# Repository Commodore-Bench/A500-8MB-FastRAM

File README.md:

# A500-8MB-FastRAM

8MB FastRAM Board for the Amiga 500 &amp; Amiga 500+

This board is based on the A600 8MB FastRAM board here: http://lvd.nedopc.com/Projects/a600_8mb/index.html

As such, the schematic is a derivative/fork of the original design, to accommodate it's usage in A500's (might also work in A1000's & A2000's).

Everything has been designed to be as easy to solder as possible, minimal surface mount, with the exception of the memory modules, but they're SOJ-42, which should be easy enough even with a basic soldering iron.

The code for the CPLD has been mostly unchanged from the original, just a single letter changed to reflect usage in the A500 as opposed to the A600, along with renaming the signal pins to something simpler.

There is only 16 MB of addressable space on 68000 CPU. This board uses half of that space, residing at $200000-$9FFFFF Zorro II memory address range. It does autoconfigure, so no need to do anything in the DOS shell.

The original design used an Altera EPM7032 5v CPLD - this has been changed for an Atmel ATF1502ASV - as these are pin-compatible replacements. 

# Bill of Materials

1 x TI TPS7333QP - https://www.mouser.co.uk/ProductDetail/Texas-Instruments/TPS7333QP?qs=sGAEpiMZZMsGz1a6aV8DcPXeWoVS0FnzG9Q6QtE79H4%3D

2 x 74AHCT157N - https://www.mouser.co.uk/ProductDetail/Texas-Instruments/SN74AHCT157N?qs=sGAEpiMZZMtxONTBFIcRfgMIbQHDmxevRGwLkGEQEjo%3D

4 x ISSI IS41LV6100D-50KLI - https://www.mouser.co.uk/ProductDetail/ISSI/IS41LV16100D-50KLI?qs=sGAEpiMZZMti5BT4iPSEnceOTYqGrIvVPVYLC4ueHfI%3D

1 x Microchip ATF1502ASV-15JU44 - https://www.digikey.co.uk/product-detail/en/microchip-technology/ATF1502ASV-15JU44/ATF1502ASV-15JU44-ND/1008571

18 x 0.1uF X7R MLCC Capacitors - https://www.mouser.co.uk/ProductDetail/Vishay/A104M15X7RF5TAA?qs=sGAEpiMZZMt3KoXD5rJ2N0XmixHAufRxOaDBAbHwq68%3D

3 x 10k Metal Film Resistors - https://www.mouser.co.uk/ProductDetail/Yageo/MFR-25FRF52-10K?qs=sGAEpiMZZMu61qfTUdNhGztMfEiwFKKTpKeEBKehEYg%3D

1 x DIP-8 Socket - https://www.mouser.co.uk/ProductDetail/Mill-Max/115-47-308-41-001000?qs=sGAEpiMZZMs%2FSh%2Fkjph1tkCPjfxlAKUmvzlAYtWANYQ%3D

2 x DIP-16 Socket - https://www.mouser.co.uk/ProductDetail/Mill-Max/115-47-316-41-001000?qs=sGAEpiMZZMs%2FSh%2Fkjph1tkCPjfxlAKUmVX4IEPiLC6M%3D

1 x DIP-64 Socket - https://www.mouser.co.uk/ProductDetail/Mill-Max/110-93-964-41-001000?qs=sGAEpiMZZMs%2FSh%2Fkjph1tvt1%2FmEPT%2FXoOM6K6uUd7C4%3D

1 x PLCC-44 Socket - https://www.mouser.co.uk/ProductDetail/Mill-Max/940-44-044-24-000000?qs=sGAEpiMZZMs%2FSh%2Fkjph1tvt1%2FmEPT%2FXokeuUw4hSJ6E%3D

2 x SIL-32 Headers - https://www.mouser.co.uk/ProductDetail/Harwin/M20-9993246?qs=sGAEpiMZZMs%252BGHln7q6pmzlZUuX%2F53qjvbFdqJAMwHI%3D

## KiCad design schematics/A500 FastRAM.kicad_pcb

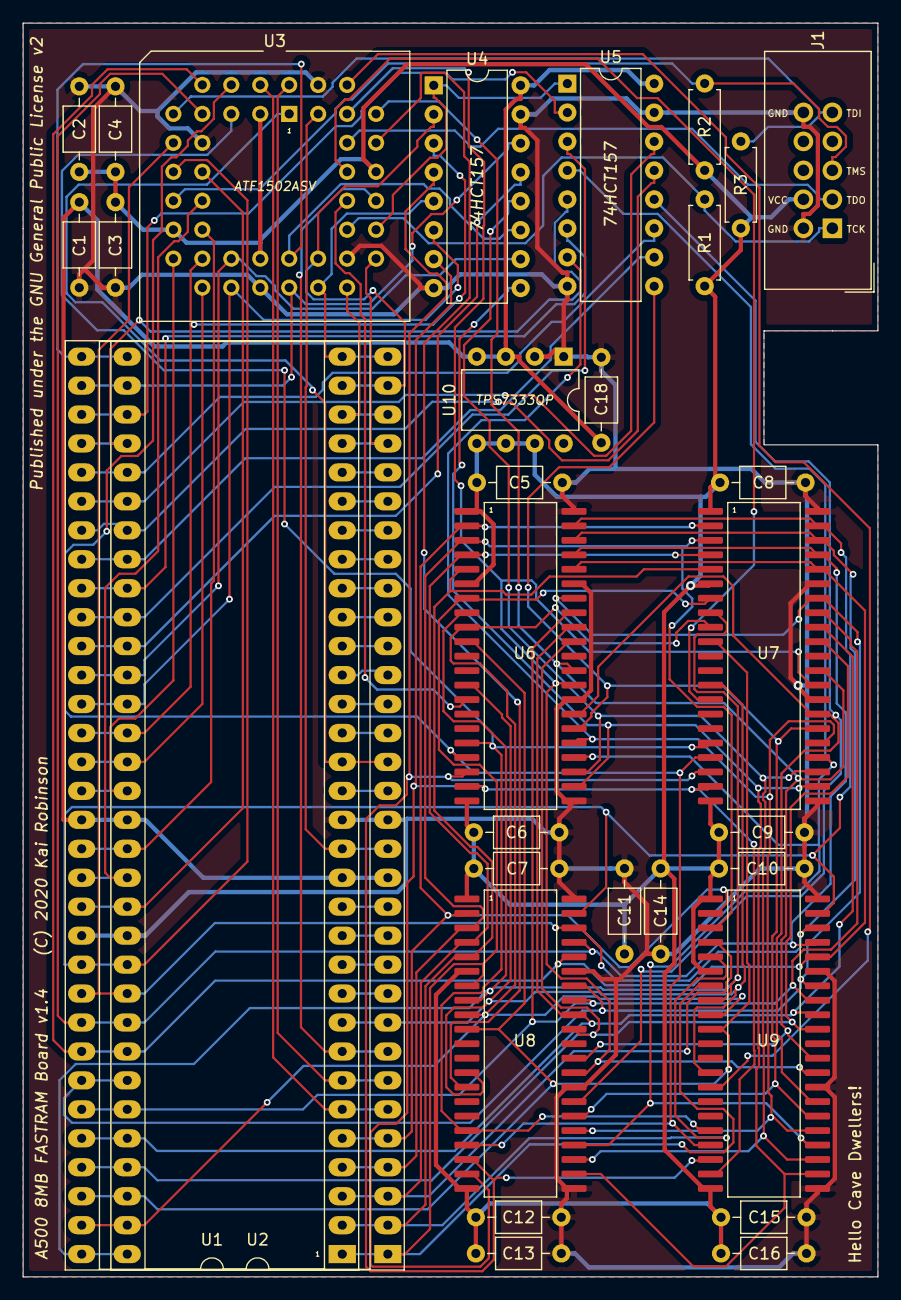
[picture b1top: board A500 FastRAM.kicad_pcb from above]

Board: 2 copper layers, 75.0 x 110.0 mm, 31 parts (0 on the bottom side), 84 nets.

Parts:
C1, C2, C3, C4, C5, C6, C7, C8, C9, C10, C11, C12, C13, C14, C15, C16, C18: 0.1uF; C_Axial_L3.8mm_D2.6mm_P7.50mm_Horizontal
J1: Microsemi_FlashPro-JTAG-10; IDC-Header_2x05_P2.54mm_Vertical
R1, R2, R3: 10k; R_Axial_DIN0207_L6.3mm_D2.5mm_P7.62mm_Horizontal
U1: 68000 Boardside; DIP-64_W22.86mm_Socket_LongPads
U2: 68000 Socket; DIP-64_W22.86mm_Socket_LongPads
U3: ATF1502ASV-15JU44; PLCC-44_THT-Socket
U4, U5: 74157; DIP-16_W7.62mm
U6, U7, U8, U9: IS41LV16100D; SOJ-42
U10: TPS7333QP; DIP-8_W7.62mm

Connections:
/CPU_A1: U1.29, U2.29, U3.29
/CPU_A2: U1.30, U2.30, U3.28
/CPU_A3: U1.31, U2.31, U3.27, U4.2
/CPU_A4: U1.32, U2.32, U3.26, U4.5
/CPU_A5: U1.33, U2.33, U3.25, U4.11
/CPU_A6: U1.34, U2.34, U3.24, U4.14
/CPU_A7: U1.35, U2.35, U5.2
/CPU_A8: U1.36, U2.36, U5.5
/CPU_A9: U1.37, U2.37, U5.11
/CPU_A10: U1.38, U2.38, U5.14
/CPU_A11: U1.39, U2.39, U5.13
/CPU_A12: U1.40, U2.40, U5.10
/CPU_A13: U1.41, U2.41, U5.6
/CPU_A14: U1.42, U2.42, U5.3
/CPU_A15: U1.43, U2.43, U4.13
/CPU_A16: U1.44, U2.44, U3.21, U4.10
/CPU_A17: U1.45, U2.45, U3.20, U4.6
/CPU_A18: U1.46, U2.46, U3.19, U4.3
/CPU_A19: U1.47, U2.47, U3.18
/CPU_A20: U1.48, U2.48, U3.17
/CPU_A21: U1.50, U2.50, U3.16
/CPU_A22: U1.51, U2.51, U3.14
/CPU_A23: U1.52, U2.52, U3.12
/CPU_AS: U1.6, U2.6, U3.2
/CPU_BERR: U1.22, U2.22
/CPU_BG: U1.11, U2.11
/CPU_BGACK: U1.12, U2.12
/CPU_BR: U1.13, U2.13
/CPU_CLK: U1.15, U2.15, U3.43
/CPU_D0: U1.5, U2.5, U6.2, U7.2, U8.2, U9.2
/CPU_D1: U1.4, U2.4, U6.3, U7.3, U8.3, U9.3
/CPU_D2: U1.3, U2.3, U6.4, U7.4, U8.4, U9.4
/CPU_D3: U1.2, U2.2, U6.5, U7.5, U8.5, U9.5
/CPU_D4: U1.1, U2.1, U6.7, U7.7, U8.7, U9.7
/CPU_D5: U1.64, U2.64, U6.8, U7.8, U8.8, U9.8
/CPU_D6: U1.63, U2.63, U6.9, U7.9, U8.9, U9.9
/CPU_D7: U1.62, U2.62, U6.10, U7.10, U8.10, U9.10
/CPU_D8: U1.61, U2.61, U6.33, U7.33, U8.33, U9.33
/CPU_D9: U1.60, U2.60, U6.34, U7.34, U8.34, U9.34
/CPU_D10: U1.59, U2.59, U6.35, U7.35, U8.35, U9.35
/CPU_D11: U1.58, U2.58, U6.36, U7.36, U8.36, U9.36
/CPU_D12: U1.57, U2.57, U3.6, U6.38, U7.38, U8.38, U9.38
/CPU_D13: U1.56, U2.56, U3.8, U6.39, U7.39, U8.39, U9.39
/CPU_D14: U1.55, U2.55, U3.9, U6.40, U7.40, U8.40, U9.40
/CPU_D15: U1.54, U2.54, U3.11, U6.41, U7.41, U8.41, U9.41
/CPU_DTACK: U1.10, U2.10
/CPU_E: U1.20, U2.20
/CPU_FC0: U1.28, U2.28
/CPU_FC1: U1.27, U2.27
/CPU_FC2: U1.26, U2.26
/CPU_HALT: U1.17, U2.17
/CPU_IPL0: U1.25, U2.25
/CPU_IPL1: U1.24, U2.24
/CPU_IPL2: U1.23, U2.23
/CPU_LDS: U1.8, U2.8, U3.33
/CPU_RESET: U1.18, U2.18, U3.1
/CPU_RW: U1.9, U2.9, U6.13, U7.13, U8.13, U9.13
/CPU_UDS: U1.7, U2.7, U3.44
/CPU_VMA: U1.19, U2.19
/CPU_VPA: U1.21, U2.21
/DRAM_A0: U3.5, U6.17, U7.17, U8.17, U9.17
/DRAM_A1: U3.4, U6.18, U7.18, U8.18, U9.18
/DRAM_A2: U4.4, U6.19, U7.19, U8.19, U9.19
/DRAM_A3: U4.7, U6.20, U7.20, U8.20, U9.20
/DRAM_A4: U4.9, U6.23, U7.23, U8.23, U9.23
/DRAM_A5: U4.12, U6.24, U7.24, U8.24, U9.24
/DRAM_A6: U5.4, U6.25, U7.25, U8.25, U9.25
/DRAM_A7: U5.7, U6.26, U7.26, U8.26, U9.26
/DRAM_A8: U5.9, U6.27, U7.27, U8.27, U9.27
/DRAM_A9: U5.12, U6.28, U7.28, U8.28, U9.28
/DRAM_LCAS: U3.39, U6.31, U7.31, U8.31, U9.31
/DRAM_RAS0: U3.34, U6.14
/DRAM_RAS1: U3.36, U7.14
/DRAM_RAS2: U3.37, U8.14
/DRAM_RAS3: U3.40, U9.14
/DRAM_UCAS: U3.41, U6.30, U7.30, U8.30, U9.30
/MUX_SWITCH: U3.31, U4.1, U5.1
/TCK: J1.1, R1.2, U3.32
/TDI: J1.9, R3.2, U3.7
/TDO: J1.3, U3.38
/TMS: J1.5, R2.2, U3.13
/VCC33: C2.2, C3.1, C4.2, C5.1, C6.1, C7.1, C8.1, C9.1, C10.1, C11.1, C12.1, C13.1, C14.1, C15.1, C16.1, J1.4, R1.1, R2.1, R3.1, U3.3, U3.15, U3.23, U3.35, U6.1, U6.6, U6.21, U7.1, U7.6, U7.21, U8.1, U8.6, U8.21, U9.1, U9.6, U9.21, U10.5, U10.6, U10.7
GND: C1.2, C2.1, C3.2, C4.1, C5.2, C6.2, C7.2, C8.2, C9.2, C10.2, C11.2, C12.2, C13.2, C14.2, C15.2, C16.2, C18.2, J1.2, J1.10, U1.16, U1.53, U2.16, U2.53, U3.10, U3.22, U3.30, U3.42, U4.8, U4.15, U5.8, U5.15, U6.22, U6.29, U6.37, U6.42, U7.22, U7.29, U7.37, U7.42, U8.22, U8.29, U8.37, U8.42, U9.22, U9.29, U9.37, U9.42, U10.1, U10.2
VCC: C1.1, C18.1, U1.14, U1.49, U2.14, U2.49, U4.16, U5.16, U10.3, U10.4

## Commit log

2019-10-02 Add files via upload
    Redoing the board renders
2019-10-02 Add files via upload
    Complete reroute of the board

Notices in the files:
schematics/A500 FastRAM.kicad_pcb:
Published under the GNU General Public License v2
(C) 2020 Kai Robinson
